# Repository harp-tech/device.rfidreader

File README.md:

# Harp RFID reader

RFID reader for 125KHz carriers.
Compible with glass capsules, buttons and cards (check pics folder).

# Licensing

The code, designs, documentation, and photos available in this repository is free: you can redistribute it and/or modify it under the terms of the used license.
Each subdirectory will contain a license or, possibly, a set of licenses if it involves both hardware and software. Check files named LICENSE.

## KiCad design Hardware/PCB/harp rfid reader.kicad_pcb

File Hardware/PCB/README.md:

## Licensing

The designs, documentation, and photos available in this repository are free: you can redistribute it and/or modify it under the terms of the used license.
Check file named LICENSE.

Copyright Filipe Carvalho 2021-2026

<br />This work is licensed under a <a rel="license" href="http://creativecommons.org/licenses/by-nc-sa/3.0/igo/">Creative Commons Attribution-NonCommercial-ShareAlike 3.0 IGO License</a>.

If your are interested in obtaining a license to sell this device, please contact filipe@oeps.tech

[1]: https://docs.google.com/spreadsheets/d/1aobmmEzBDethzIlrm1eg0eYkBqlyX3s9WbA9KgRwVQI/edit?usp=sharing

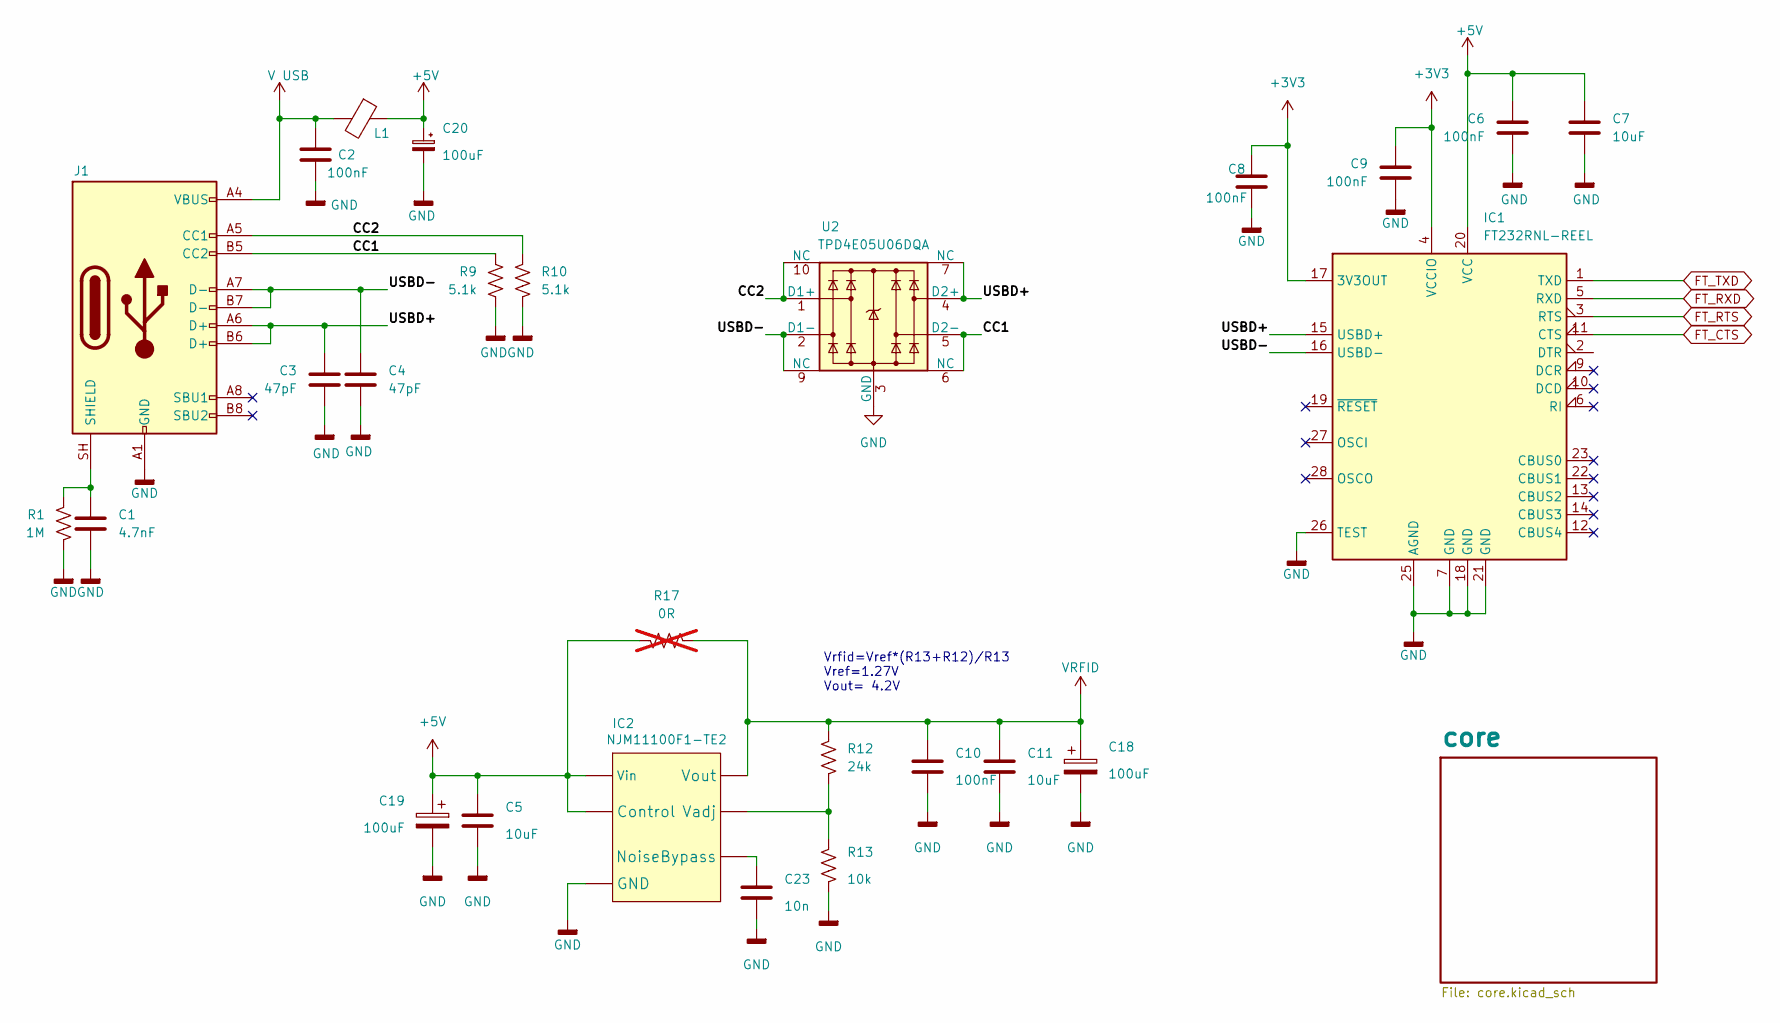
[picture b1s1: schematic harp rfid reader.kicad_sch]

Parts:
C1: 4.7nF; C_0402_1005Metric; Voltage 100V; Tolerance ±10%; MPN 885012205084
C2, C6, C8, C9, C10: 100nF; C_0402_1005Metric; Tolerance ±10%; Voltage 50V; MPN CGA2B3X7R1H104K050BB
C3, C4: 47pF; C_0402_1005Metric; Voltage 50V; Tolerance ±5%; MPN 04025A470JAT2A
C5, C7, C11: 10uF; C_0603_1608Metric; Voltage 16V; Tolerance ±20%; MPN EMK107BBJ106MA-T
C18, C19, C20: 100uF; C_1206_3216Metric; Tolerance ±20%; Voltage 10V; MPN TLJA107M010R1400
C23: 10n; C_0402_1005Metric; Tolerance ±10%; Voltage 25V; MPN GRM155R71E103KA01D
IC1: FT232RNL-REEL; SSOP-28_5.3x10.2mm_P0.65mm; MPN FT232RNL-REEL
IC2: NJM11100F1-TE2; SOT-23-6; MPN NJM11100F1-TE2
J1: USB4105-GF-A; USB_C_Receptacle_GCT_USB4105-xx-A_16P_TopMnt_Horizontal; MPN USB4105-GF-A
L1: MI0805K400R-10; R_0805_2012Metric; MPN MI0805K400R-10
R1: 1M; R_0402_1005Metric; Tolerance ±1%; MPN CRCW04021M00FKED
R9, R10: 5.1k; R_0402_1005Metric; Tolerance ±1%; MPN ERJ-2RKF5101X
R12: 24k; R_0402_1005Metric; Tolerance ±0.1%; MPN ERA-2AEB243X
R13: 10k; R_0402_1005Metric; Tolerance ±0.1%; MPN CPF0402B10KE1
R17: 0R; R_0402_1005Metric; MPN DNP; not fitted
U2: TPD4E05U06DQA; USON-10_2.5x1.0mm_P0.5mm; MPN TPD4E05U06DQAR

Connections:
+3V3: C8.1, C9.1, IC1.4 (VCCIO), IC1.17 (3V3OUT); also elsewhere on the board
+5V: C5.1, C6.1, C7.1, C19.1, C20.1, IC1.20 (VCC), IC2.1 (Control), IC2.6 (Vin), L1.1, R17.1; also elsewhere on the board
/CC1: J1.B5 (CC2), R9.1, U2.5 (D2-), U2.6 (NC)
/CC2: J1.A5 (CC1), R10.1, U2.1 (D1+), U2.10 (NC)
/USBD+: C3.1, IC1.15 (USBD+), J1.A6 (D+), J1.B6 (D+), U2.4 (D2+), U2.7 (NC)
/USBD-: C4.1, IC1.16 (USBD-), J1.A7 (D-), J1.B7 (D-), U2.2 (D1-), U2.9 (NC)
FT_CTS: IC1.11 (CTS); also elsewhere on the board
FT_RTS: IC1.3 (RTS); also elsewhere on the board
FT_RXD: IC1.5 (RXD); also elsewhere on the board
FT_TXD: IC1.1 (TXD); also elsewhere on the board
GND: C1.2, C2.2, C3.2, C4.2, C5.2, C6.2, C7.2, C8.2, C9.2, C10.2, C11.2, C18.2, C19.2, C20.2, C23.2, IC1.7 (GND), IC1.18 (GND), IC1.21 (GND), IC1.25 (AGND), IC1.26 (TEST), IC2.2 (GND), J1.A1 (GND), J1.A12 (GND), J1.B1 (GND), J1.B12 (GND), R1.2, R9.2, R10.2, R13.2, U2.3 (GND), U2.8 (GND); also elsewhere on the board
unnamed: C23.1, IC2.3 (NoiseBypass)
unnamed: IC2.5 (Vadj), R12.2, R13.1
unnamed: C1.1, J1.SH (SHIELD), R1.1
V USB: C2.1, J1.A4 (VBUS), J1.A9 (VBUS), J1.B4 (VBUS), J1.B9 (VBUS), L1.2
VRFID: C10.1, C11.1, C18.1, IC2.4 (Vout), R12.1, R17.2; also elsewhere on the board

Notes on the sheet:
Vrfid=Vref*(R13+R12)/R13 Vref=1.27V Vout= 4.2V

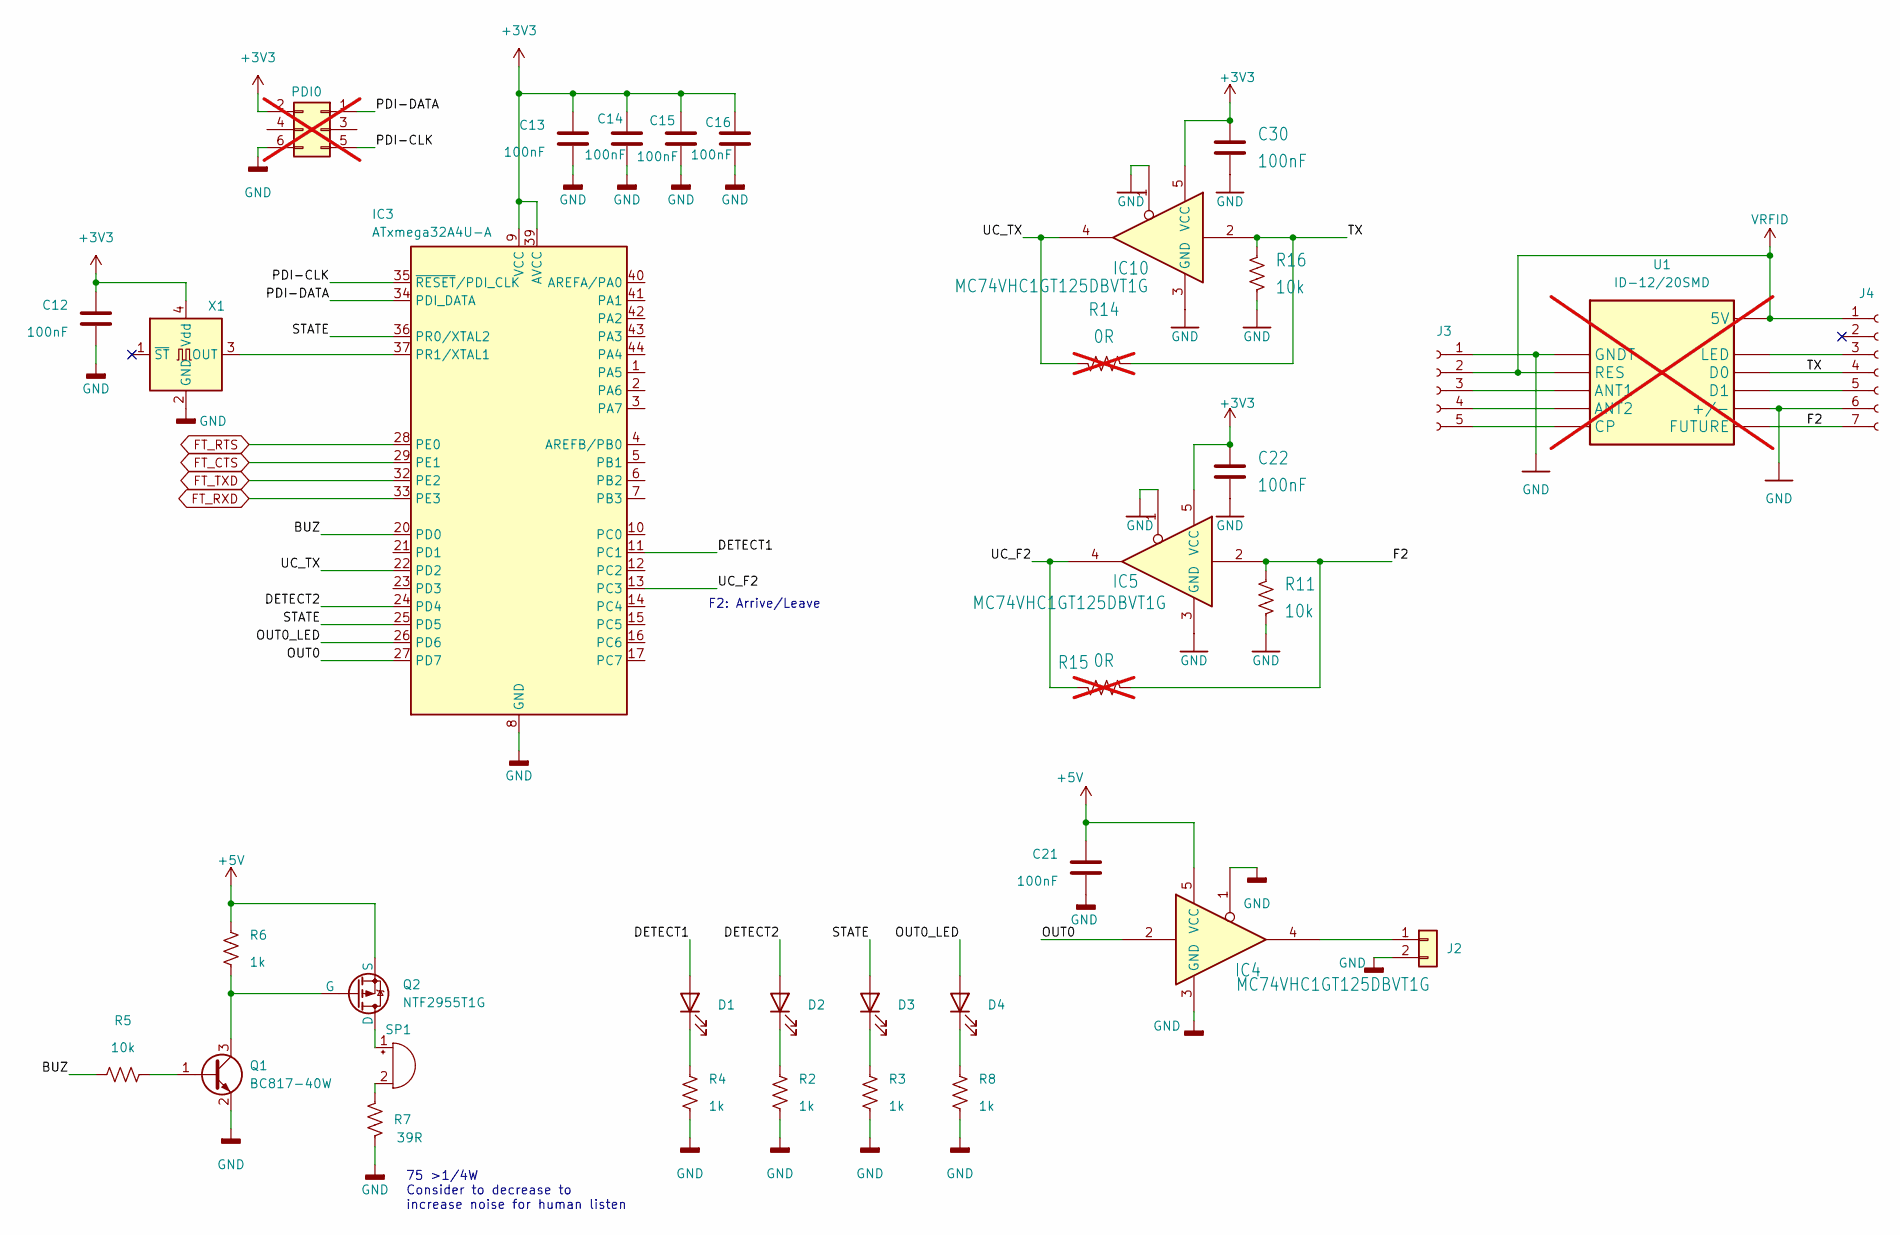
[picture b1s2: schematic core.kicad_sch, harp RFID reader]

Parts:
C12, C13, C14, C15, C16, C21, C22, C30: 100nF; C_0402_1005Metric; Tolerance ±10%; Voltage 50V; MPN CGA2B3X7R1H104K050BB
D1, D2, D3, D4: 5975004407F; LED_0603_1608Metric; MPN 5975004407F
IC3: ATxmega32A4U-A; TQFP-44_10x10mm_P0.8mm; MPN ATXMEGA32A4U-A
IC4, IC5, IC10: MC74VHC1GT125DBVT1G; SOT-353_SC-70-5; MPN MC74VHC1GT125DBVT1G
J2: 282834-2; 22-23-2021; MPN 282834-2
J3: NPPN051BFLD-RC; PinSocket_1x05_P2.00mm_Vertical_SMD_Pin1Right; MPN NPPN051BFLD-RC
J4: NPPN071BFLC-RC; PinSocket_1x07_P2.00mm_Vertical_SMD_Pin1Right; MPN NPPN071BFLC-RC
PDI0: 67996-206HLF; PinHeader_2x03_P2.54mm_Vertical; MPN 67996-206HLF; not fitted
Q1: BC817-40W; SOT-323_SC-70; Voltage 45V; MPN BC817-40W-7
Q2: NTF2955T1G; SOT-223; Voltage 60V; MPN NTF2955T1G
R2, R3, R4, R6, R8: 1k; R_0402_1005Metric; Tolerance ±1%; MPN CRCW04021K00FKED
R5, R11, R16: 10k; R_0402_1005Metric; Tolerance ±0.1%; MPN CPF0402B10KE1
R7: 39R; R_0402_1005Metric; Tolerance ±1%; MPN RCS040239R0FKED
R14, R15: 0R; R_0402_1005Metric; MPN DNP; not fitted
SP1: SMT-0540-S-R; BUZZER-COIL_SMT-0540-S-R; MPN SMT-0540-S-R
U1: ID-12/20SMD; ID-12_SMD body; MPN ID-12LA; not fitted
X1: O 32,0-JT32C-A-K-3,3-LF; CNP-MISCELLANEOUS_OSCILLATOR_3.2X2.5; MPN O 32,0-JT32C-A-K-3,3-LF

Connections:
+3V3: C12.1, C13.1, C14.1, C15.1, C16.1, C22.1, C30.1, IC3.9 (VCC), IC3.19 (VCC), IC3.31 (VCC), IC3.39 (AVCC), IC5.5 (VCC), IC10.5 (VCC), PDI0.2, X1.4 (Vdd); also elsewhere on the board
+5V: C21.1, IC4.5 (VCC), Q2.3 (S), R6.1; also elsewhere on the board
/core/BUZ: IC3.20 (PD0), R5.1
/core/DETECT1: D1.2 (A), IC3.11 (PC1)
/core/DETECT2: D2.2 (A), IC3.24 (PD4)
/core/F2: IC5.2, J4.7, R11.1, R15.2, U1.6 (FUTURE)
/core/OUT0: IC3.27 (PD7), IC4.2
/core/OUT0_LED: D4.2 (A), IC3.26 (PD6)
/core/PDI-CLK: IC3.35 (~RESET/PDI_CLK), PDI0.5
/core/PDI-DATA: IC3.34 (PDI_DATA), PDI0.1
/core/STATE: D3.2 (A), IC3.25 (PD5), IC3.36 (PR0/XTAL2)
/core/TX: IC10.2, J4.4, R14.2, R16.1, U1.9 (D0)
/core/UC_F2: IC3.13 (PC3), IC5.4, R15.1
/core/UC_TX: IC3.22 (PD2), IC10.4, R14.1
FT_CTS: IC3.29 (PE1); also elsewhere on the board
FT_RTS: IC3.28 (PE0); also elsewhere on the board
FT_RXD: IC3.33 (PE3); also elsewhere on the board
FT_TXD: IC3.32 (PE2); also elsewhere on the board
GND: C12.2, C13.2, C14.2, C15.2, C16.2, C21.2, C22.2, C30.2, IC3.8 (GND), IC3.18 (GND), IC3.30 (GND), IC3.38 (GND), IC4.1, IC4.3 (GND), IC5.1, IC5.3 (GND), IC10.1, IC10.3 (GND), J2.2, J3.1, J4.6, PDI0.6, Q1.2 (E), R2.1, R3.1, R4.1, R7.2, R8.1, R11.2, R16.2, U1.1 (GNDT), U1.7 (+/-), X1.2 (GND); also elsewhere on the board
unnamed: D1.1 (K), R4.2
unnamed: D2.1 (K), R2.2
unnamed: D3.1 (K), R3.2
unnamed: D4.1 (K), R8.2
unnamed: IC3.37 (PR1/XTAL1), X1.3 (OUT)
unnamed: IC4.4, J2.1
unnamed: J3.3, U1.3 (ANT1)
unnamed: J3.4, U1.4 (ANT2)
unnamed: J3.5, U1.5 (CP)
unnamed: J4.3, U1.10 (LED)
unnamed: J4.5, U1.8 (D1)
unnamed: Q1.1 (B), R5.2
unnamed: Q1.3 (C), Q2.1 (G), R6.2
unnamed: Q2.2 (D), Q2.4 (D), SP1.1 (+)
unnamed: R7.1, SP1.2 (-)
VRFID: J3.2, J4.1, U1.2 (RES), U1.11 (5V); also elsewhere on the board

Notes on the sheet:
F2: Arrive/Leave
75 >1/4W Consider to decrease to increase noise for human listen

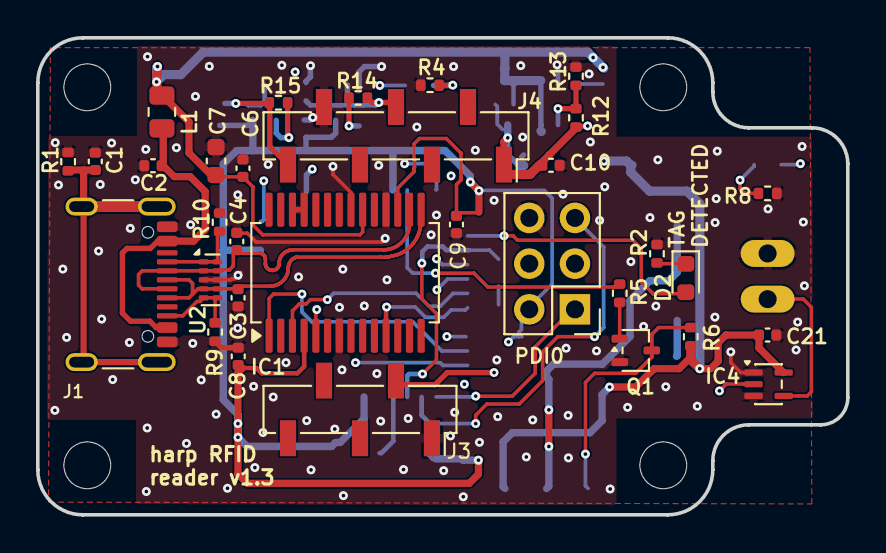
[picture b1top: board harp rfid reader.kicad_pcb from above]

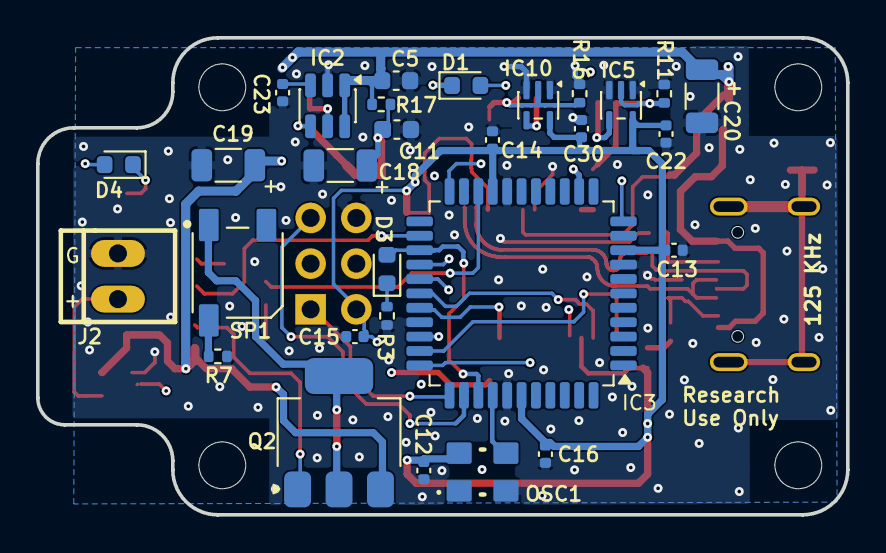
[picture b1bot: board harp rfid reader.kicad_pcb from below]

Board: 4 copper layers, 45.0 x 26.5 mm, 65 parts (29 on the bottom side), 38 nets.

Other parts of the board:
UNK_HOLE_1: dummyfp1
UNK_HOLE_2, UNK_HOLE_2#2: dummyfp2
UNK_HOLE_3: dummyfp3

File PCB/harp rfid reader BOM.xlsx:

Qty | Value | Package | Parts | MPN | Type | Distributor | Distributor PN
ASSEMBLY HOUSE
2 | 47pF | C0402 | C3, C4 | 04025A470JAT2A | SMD | Digikey | 478-1078-6-ND
1 | 4.7nF | C0402 | C1 | 885012205084 | SMD | Digikey | 732-12234-6-ND
11 | 100nF 50V X7R 10% | C0402 | C2, C6, C8, C9, C10, C12, C13, C14, C15, C16, C21 | CGA2B3X7R1H104K050BB | SMD | Digikey | 445-6899-6-ND
4 | 10uF 20% 16V X5R | C0603 | C5, C7, C11, C17 | EMK107BBJ106MA-T | SMD | Digikey | 587-3238-6-ND
3 | 100uF 20% 10V | CT3216 | C18, C19, C20 | 298W107X0010Q2D | SMD | Digikey | 718-298W107X0010Q2DDKR-ND
1 | 39Ω 1/5watt 1% 0402 | R0402 | R7 | RCS040239R0FKED | SMD | Digikey | 541-10407-6-ND
5 | 1k | R0402 | R2, R3, R4, R6, R8 | CRCW04021K00FKED | SMD | Digikey | 541-1.00KLDKR-ND
1 | 10k | R0402 | R5 | CRCW040210K0FKED | SMD | Digikey | 541-10.0KLDKR-ND
1 | 1M | R0402 | R1 | CRCW04021M00FKED | SMD | Digikey | 541-1.00MLDKR-ND
1 | 40ohms 100MHz 1.5A 0805 SMD | L0805 | L1 | MI0805K400R-10 | SMD | Digikey | 240-2389-6-ND
1 | TRANS NPN 45V 0.5A | SC70-3 | Q1 | BC817-40W-7 | SMD | Digikey | BC817-40WDIDKR-ND
1 | MOSFET P-CH 60V 1.7A | SOT223 | Q2 | NTF2955T1G | SMD | Digikey | NTF2955T1GOSDKR-ND
4 | RED LED | LED0603 | TAG_B, TAG_T, STATE, OUT0 | 5975004407F | SMD | Digikey | 350-2950-6-ND
1 | Buzzers Transducer 3V 100mA 4kHz 78dB @ 3V |  | SP1 | SMT-0540-S-R | SMD | Digikey | 668-1060-6-ND
1 | USB to UART USB 2.0 | 28-SSOP | IC1 | FT232RL-REEL | SMD | Digikey | 768-1007-6-ND
1 | Ultra-Low-Noise LDO 3.3V 250mA | SOT-23-5 | IC2 | LP5907MFX-3.3/NOPB | SMD | Digikey | 296-38557-6-ND
1 | ATXMEGA32A4U | 44-TQFP | IC3 | ATXMEGA32A4U-AUR | SMD | Digikey | ATXMEGA32A4U-AURDKR-ND
1 | IC BUFFER NON-INVERT 5.5V | TSOP-5 | IC4 | M74VHC1GT126DT1G | SMD | Digikey | M74VHC1GT126DT1GOSDKR-ND |  |  |  |  |  | Check R7 value used
1 | 32 MHz CMOS | 4-SMD | OSC1 | O 32,0-JT32C-A-K-3,3-LF | SMD | Digikey | 1908-1044-6-ND
1 | CONN RCPT USB2.0 MINI |  | USB | UX60-MB-5S8 | SMD | Digikey | H2960DKR-ND
1 | CONN RCPT 5POS 0.1 GOLD SMD |  | U1 5POS | NPPN051BFLD-RC‎ | SMD | Digikey | ‎S5902-05-ND‎
1 | CONN RCPT 7POS 0.1 GOLD SMD |  | U1 7POS | ‎NPPN071BFLC-RC‎ | SMD | Digikey | ‎S5901-07-ND‎
1 | CONN Terminal block 2.54MM |  | OUT | 282834-2 | TH | Digikey | A98333-ND
POST-PRODUCTION
1 | RFID Reader ID-12LA (125 kHz) |  |  | ID-12LA | - | SparkFun | SEN-11827
NOTES
 |  |  |  | Number of unique parts | 23
 |  |  |  | Number of SMD parts | 45
 |  |  |  | Number of TH parts | 1

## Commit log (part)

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2021-02-19 Created README.md
2021-02-19 Added first PCB files.
2021-02-19 Added compatible devices.
2021-02-21 Added first firmware files.
2021-02-21 Increased oscillator and buzzer pads.
2021-02-21 Replaced microcontroller.
2021-02-26 Updated firmware.
2021-02-26 Correct footprints of buzzer and oscillator.
2021-02-26 Added the bootloader for ATXMEGA32A4U.
2021-05-03 Minor PCB corrections.
2021-05-03 Added 3 new capacitors.
2022-05-06 Corrected STATE and DETECT lines and increased LED resistors.
2022-05-06 Remapped TOP LED to PC1.
2022-05-08 Added new event and renamed reserved registers.
    New event: (REG 33 U64) TAG_ID_LEAVED -> When tag leaves the detection zone.
2022-05-08 Increased harp core version and changed microcontroller.
    Increased harp core to version 1.9 and changed microcontroller to ATXMEGA32A4U.
2022-05-09 Increased hardware version to match the current PCB version.
2022-05-25 Added a digital output.
2022-09-13 Added fabrication files and updated BOM.
2022-09-13 Added mechanical dimensions.
2022-09-13 Export mechanical dimensions.
2022-09-13 Added more details to mechanical dimensions file.
2022-09-13 Minor BOM correction.
2022-11-03 Minor corrections.
2022-11-07 Released firmware version 0.1.
2022-12-07 Added new registers to handle the digital output.
2022-12-07 Added routines to handle the digital output.
2022-12-07 Updated default timing.
2022-12-07 Ability to turn LEDs off.
2022-12-07 Increased firmware version to 0.2.
2022-12-07 Deleted .hex files from the repository.
2022-12-27 Removed unnecessary files.
2022-12-27 Refactored hardware files.
2022-12-27 Added .gitignore to individual folders.
2022-12-27 Renamed pics folder to Assets.
2022-12-27 Renamed files.
2022-12-28 Updated to atxmega core version 1.12.
    Also leave the default timestamp offset configured to 3 (1.5 ms).
2022-12-28 Increased firmware version to 1.0
2023-03-10 Added antenna datasheets.
2023-04-18 Add interface generators
2023-04-18 Add first draft of device schema
2023-04-18 Add automatically generated bonsai interface
2023-04-19 Change device name
2023-04-20 Favor "PulseWidth" over "PulseDuration"
2023-04-21 Fixed bad bitmasks.
    The notification and trigger bitmasks where corrected.
2023-04-22 Update schema bitMasks according to #2
2023-04-24 Reduce verbosity
2023-06-02 Improve schema readability
2023-06-02 Update `Device` classes to new schema
2023-07-05 Increased firmware version to 1.1.
2023-07-05 Added ability to also read the ISO11785 tags.
2023-08-10 Add minor clarifications to device schema
2023-08-10 Update interface to use latest generators
2023-08-10 Add interface license and package stable version
2023-08-10 Updated firmware version.
2023-08-10 Updated harp core to 1.13.
2023-09-04 Added excel file explaining how to parse the ID.
2023-09-06 Increase firmware version.
2023-09-06 Reversed ID bits and apply calculation.
2024-01-25 Increased firmware version to 1.3.
2024-01-25 Clear tag register after the tag leaves the detection zone. Fix #7
    For the ISO 11785 the register is cleared after detection because there's no indication of when the tag leaves.
2024-01-26 Increased firmware version to 1.3
2025-06-12 Create basic CI/CD for interface package
2025-06-27 First Makefile.
    Trying to create a Makefile.
    Apparently, it compiles well.
    I haven't tried sending the .hex to a device yet.
2025-10-22 Updated to atxmega core 1.15
